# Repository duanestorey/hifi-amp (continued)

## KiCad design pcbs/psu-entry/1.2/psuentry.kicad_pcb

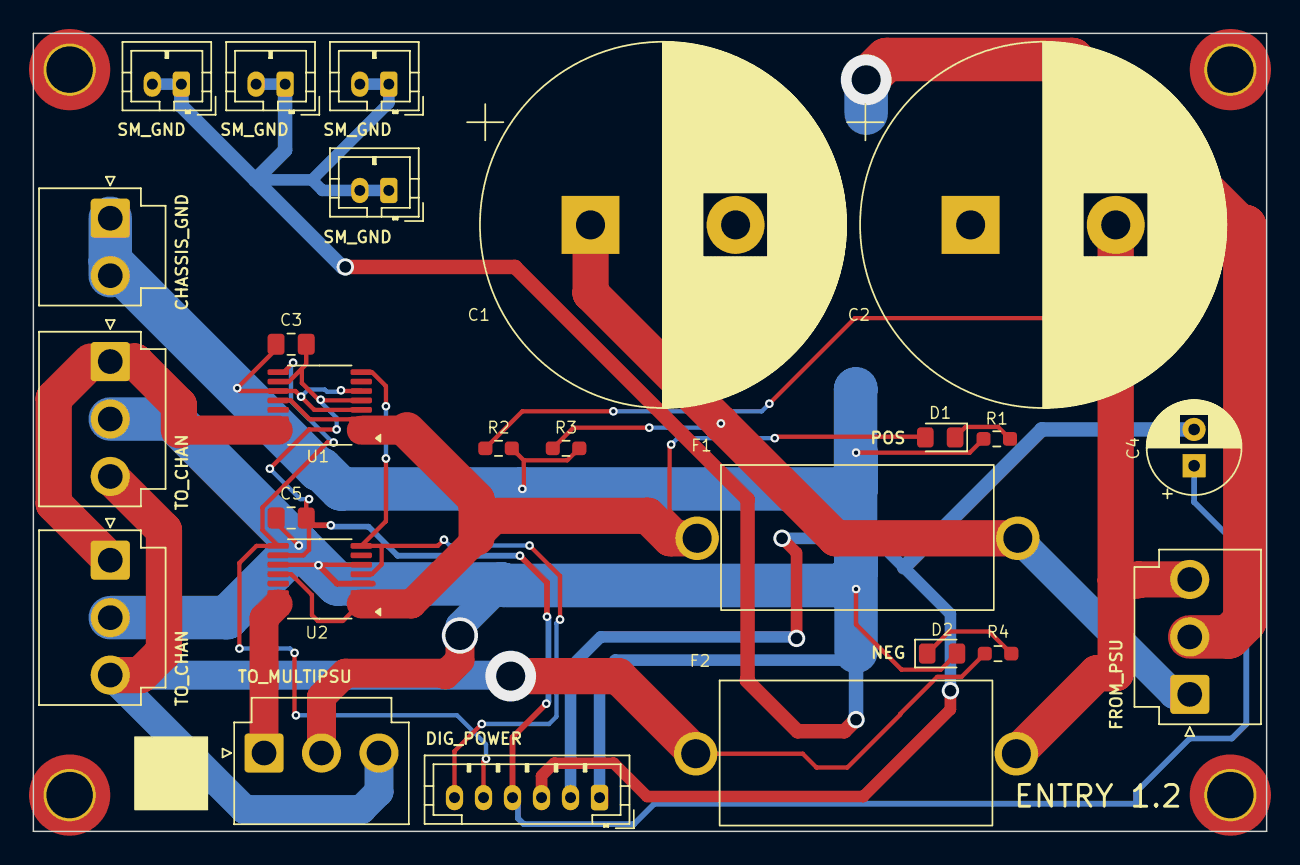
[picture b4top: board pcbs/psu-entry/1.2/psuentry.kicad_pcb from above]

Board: 2 copper layers, 85.0 x 55.0 mm, 29 parts (0 on the bottom side), 12 nets.

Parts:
C1, C2: 10000u 50V; CP_Radial_D25.0mm_P10.00mm_SnapIn
C3, C5: 0.1u; C_0805_2012Metric_Pad1.18x1.45mm_HandSolder
C4: 220u 10V; CP_Radial_D6.3mm_P2.50mm
D1, D2: YELLOW; LED_0805_2012Metric_Pad1.15x1.40mm_HandSolder
F1, F2: Fuse_Small; Aliexpress Fuse 5x20
H1, H2, H3, H4: MountingHole; MountingHole_3.2mm_M3_DIN965_Pad_TopOnly
J1, J2, J3, J4: Conn_01x02_Pin; JST_PH_B2B-PH-K_1x02_P2.00mm_Vertical
J5: Conn_01x02_Pin; JST_VH_B2P-VH-B_1x02_P3.96mm_Vertical
J6, J7, J8, J9: Conn_01x03_Pin; JST_VH_B3P-VH-B_1x03_P3.96mm_Vertical
J10: Conn_01x06_Pin; JST_PH_B6B-PH-K_1x06_P2.00mm_Vertical
R1, R4: 3.6K; R_0603_1608Metric_Pad0.98x0.95mm_HandSolder
R2, R3: 20K; R_0603_1608Metric_Pad0.98x0.95mm_HandSolder
U1, U2: INA260; TSSOP-16_4.4x5mm_P0.65mm

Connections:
3V3: C3.2, C4.1, C5.2, J10.4, U1.5 (A0), U1.10 (VS), U2.10 (VS)
DC_NEG: C2.2, F2.2, J8.3, R2.1
DC_NEG_FUSED: F2.1, J6.3, J7.3, J9.3, R4.2
DC_POS: C1.1, F1.2, J8.1, R3.1
DC_POS_FUSED: D1.2 (A), F1.1, U1.1 (IN+), U1.2 (IN+), U1.3 (IN+), U1.12 (VBUS), U2.1 (IN+), U2.2 (IN+), U2.3 (IN+), U2.12 (VBUS)
DC_POS_POW: J6.1, J7.1, U1.14 (IN-), U1.15 (IN-), U1.16 (IN-)
DC_POS_PSU_POW: J9.1, U2.14 (IN-), U2.15 (IN-), U2.16 (IN-)
unnamed: D1.1 (K), R1.1
unnamed: D2.1 (K), R4.1
PGND: C1.2, C2.1, C3.1, C4.2, C5.1, D2.2 (A), J1.1, J1.2, J2.1, J2.2, J3.1, J3.2, J4.1, J4.2, J5.1, J5.2, J6.2, J7.2, J8.2, J9.2, J10.1, J10.2, J10.3, R1.2, R2.2, R3.2, U1.4 (A1), U1.6 (GND), U1.11 (GND), U2.4 (A1), U2.6 (GND), U2.11 (GND)
SCL: J10.5, U1.9 (SCL), U2.9 (SCL)
SDA: J10.6, U1.8 (SDA), U2.5 (A0), U2.8 (SDA)

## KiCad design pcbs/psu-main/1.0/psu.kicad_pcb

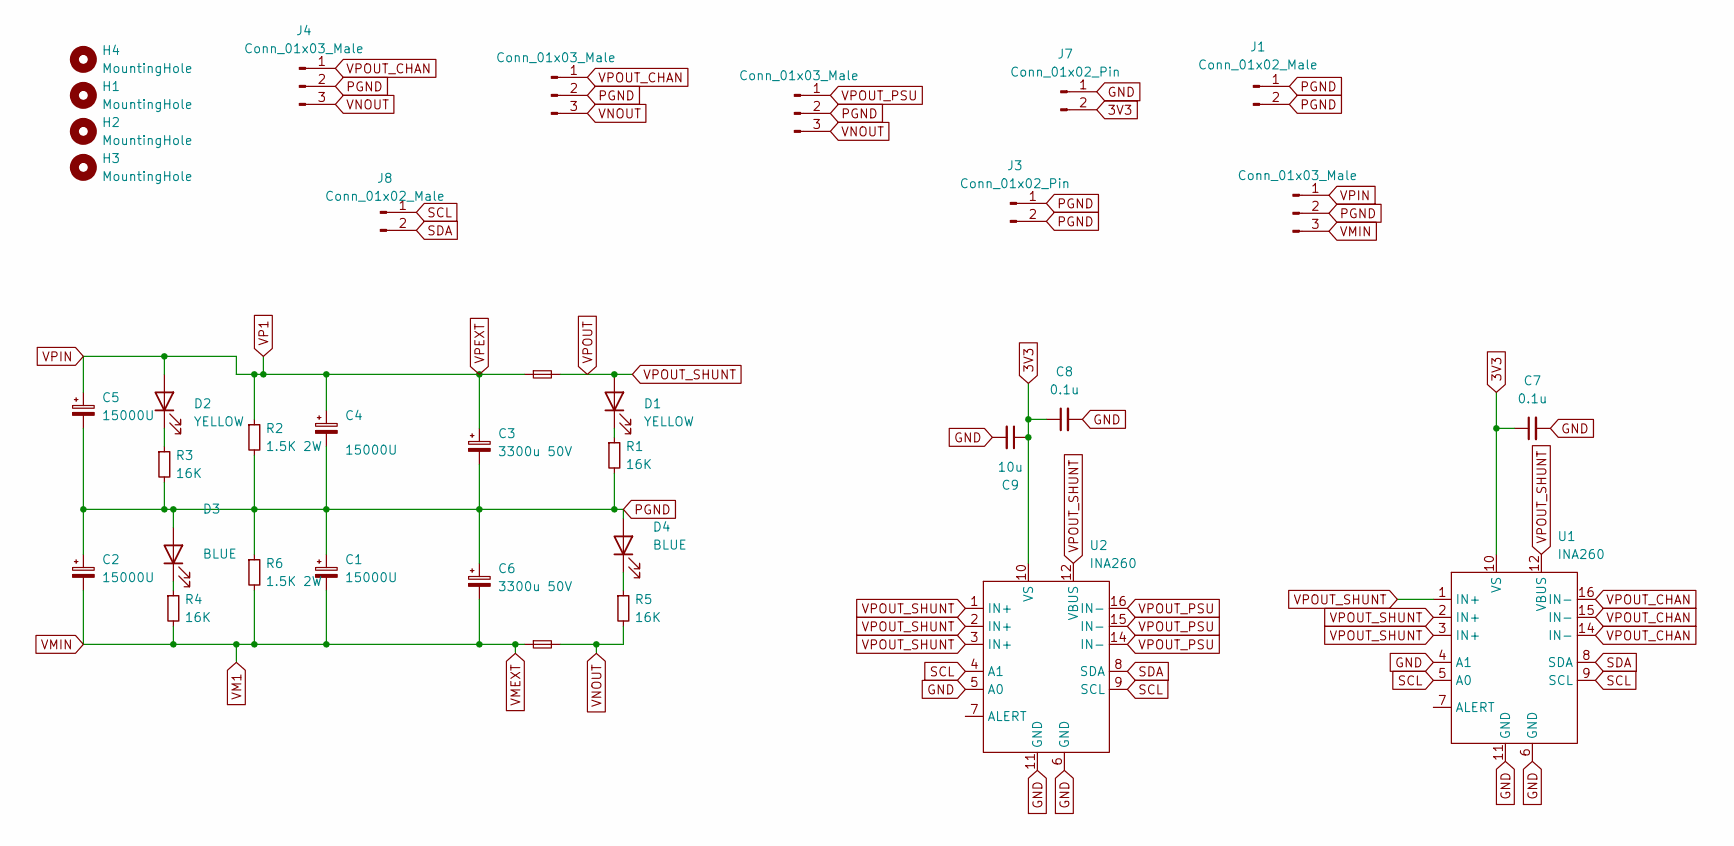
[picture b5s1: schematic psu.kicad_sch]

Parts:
C1, C2, C4, C5: 15000U; CP_Radial_D30.0mm_P10.00mm_SnapIn
C3, C6: 3300u 50V; CP_Radial_D16.0mm_P7.50mm
C7, C8: 0.1u; C_0805_2012Metric_Pad1.18x1.45mm_HandSolder
C9: 10u; C_1206_3216Metric_Pad1.33x1.80mm_HandSolder
D1, D2: YELLOW; LED_0603_1608Metric_Pad1.05x0.95mm_HandSolder
D3, D4: BLUE; LED_0603_1608Metric_Pad1.05x0.95mm_HandSolder
F1, F2: Fuse_Small; Aliexpress Fuse 5x20
H1, H2, H3, H4: MountingHole; MountingHole_3mm_Pad_TopOnly
J1: Conn_01x02_Male; JST_VH_B2P-VH-B_1x02_P3.96mm_Vertical
J2, J4, J5, J6: Conn_01x03_Male; JST_VH_B3P-VH_1x03_P3.96mm_Vertical
J3, J7: Conn_01x02_Pin; JST_PH_B2B-PH-K_1x02_P2.00mm_Vertical
J8: Conn_01x02_Male; JST_PH_B2B-PH-K_1x02_P2.00mm_Vertical
R1, R3, R4, R5: 16K; LED_0603_1608Metric_Pad1.05x0.95mm_HandSolder; Mouser 71-CRCW060316K0FKEAC
R2, R6: 1.5K 2W; R_2512_6332Metric_Pad1.40x3.35mm_HandSolder; Mouser 652-CRM2512JW152ELF
U1, U2: INA260; TSSOP-16_4.4x5mm_P0.65mm; Mouser 595-INA260AIPWR

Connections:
3V3: C7.1, C8.1, C9.1, J7.2, U1.10 (VS), U2.10 (VS)
GND: C7.2, C8.2, C9.2, J7.1, U1.4 (A1), U1.6 (GND), U1.11 (GND), U2.5 (A0), U2.6 (GND), U2.11 (GND)
unnamed: D1.1 (K), R1.1
unnamed: D2.1 (K), R3.1
unnamed: D3.1 (K), R4.1
unnamed: D4.1 (K), R5.1
PGND: C1.1, C2.1, C3.2, C4.2, C5.2, C6.1, D3.2 (A), D4.2 (A), J1.1, J1.2, J2.2, J3.1, J3.2, J4.2, J5.2, J6.2, R1.2, R2.2, R3.2, R6.1
SCL: J8.1, U1.5 (A0), U1.9 (SCL), U2.4 (A1), U2.9 (SCL)
SDA: J8.2, U1.8 (SDA), U2.8 (SDA)
VM1: C1.2, C2.2, C6.2, F2.1, J2.3, R4.2, R6.2
VNOUT: F2.2, J4.3, J5.3, J6.3, R5.2
VP1: C3.1, C4.1, C5.1, D2.2 (A), F1.1, J2.1, R2.1
VPOUT: D1.2 (A), F1.2, U1.1 (IN+), U1.2 (IN+), U1.3 (IN+), U1.12 (VBUS), U2.1 (IN+), U2.2 (IN+), U2.3 (IN+), U2.12 (VBUS)
VPOUT_CHAN: J4.1, J5.1, U1.14 (IN-), U1.15 (IN-), U1.16 (IN-)
VPOUT_PSU: J6.1, U2.14 (IN-), U2.15 (IN-), U2.16 (IN-)

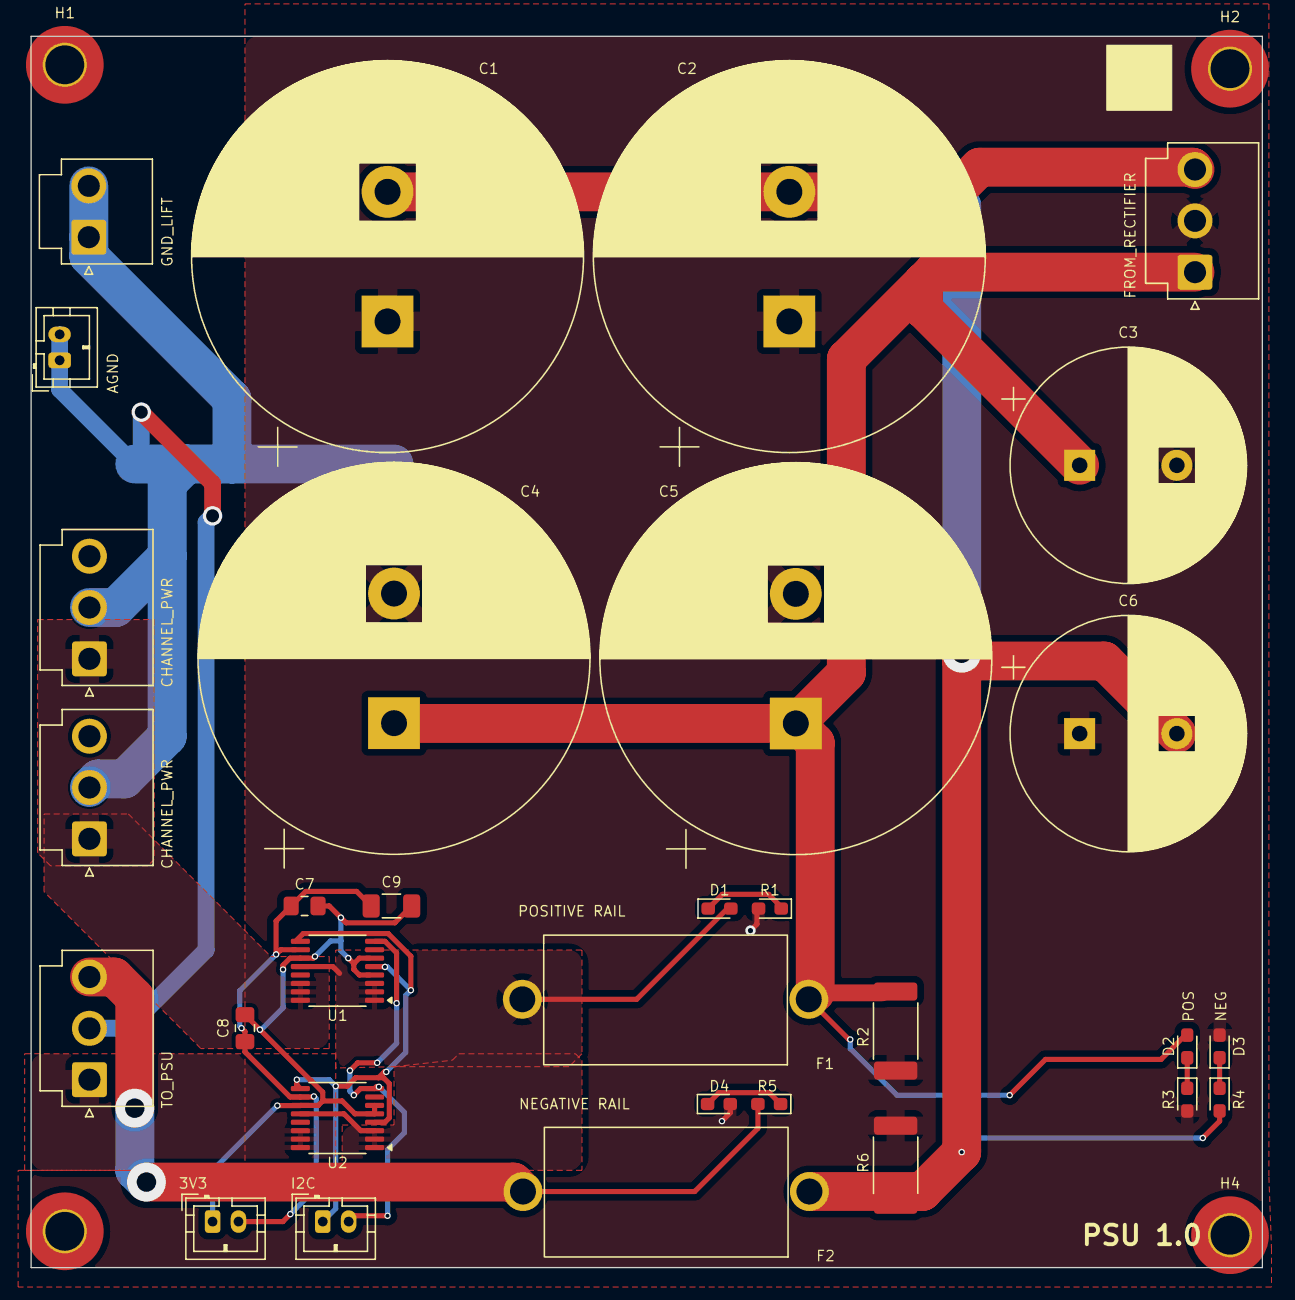
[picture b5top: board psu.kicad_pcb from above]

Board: 2 copper layers, 95.0 x 95.0 mm, 35 parts (0 on the bottom side), 15 nets.
